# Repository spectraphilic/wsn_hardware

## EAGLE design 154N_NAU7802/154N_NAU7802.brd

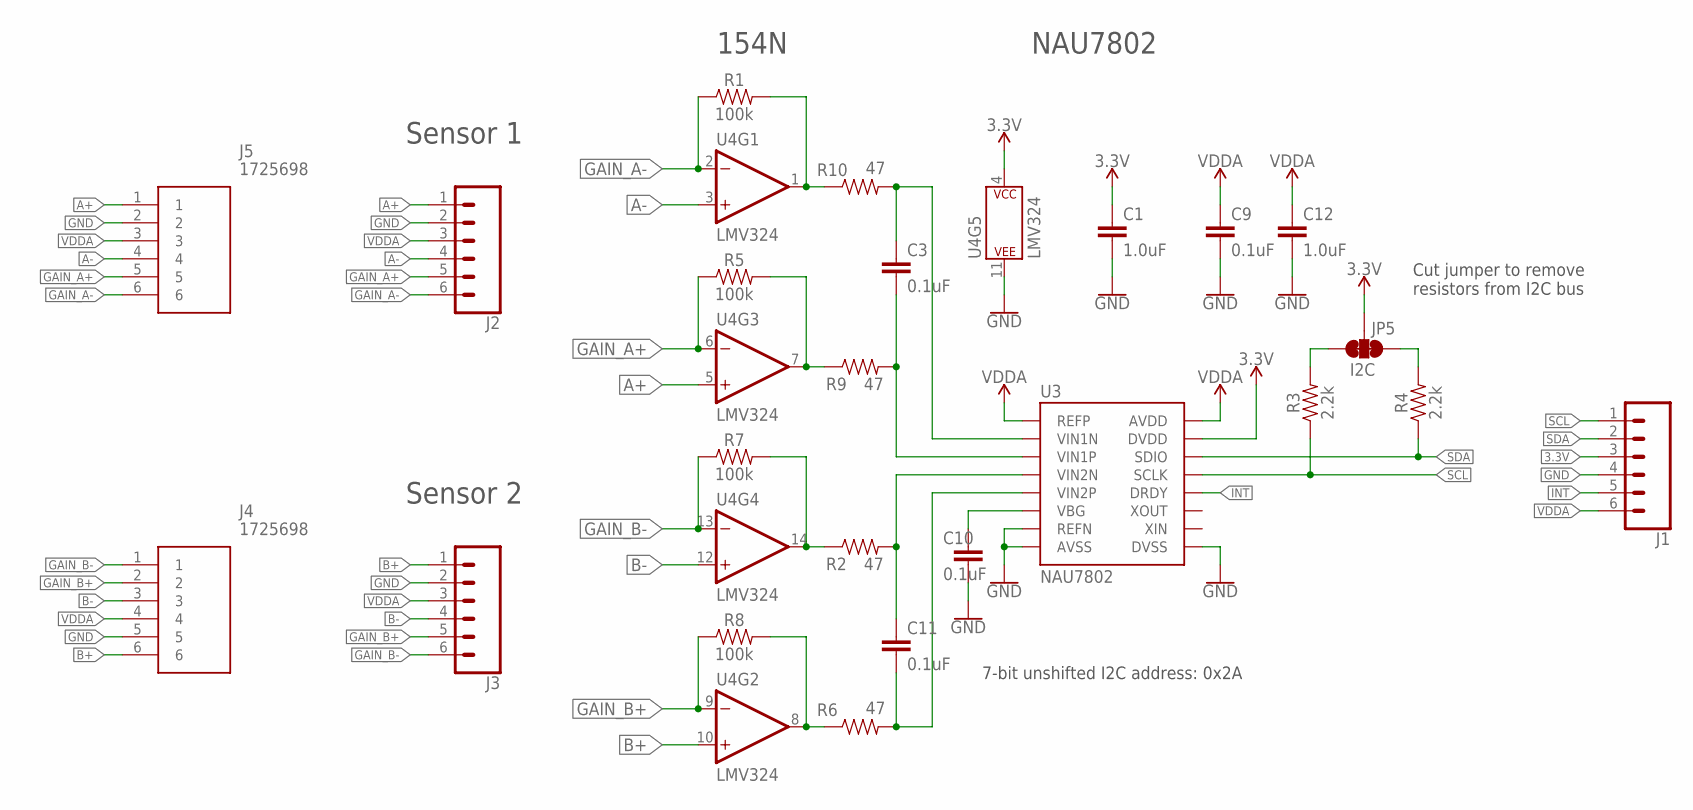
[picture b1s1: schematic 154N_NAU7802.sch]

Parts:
C1, C12: 1.0uF; 0603
C3, C9, C10, C11: 0.1uF; 0603
J1, J2, J3: CONN_06SILK_FEMALE_PTH; 1X06
J4, J5: 1725698; SHDR6W90P0X254_1X6_1570X620X85
JP5: I2C; SMT-JUMPER_3_2-NC_TRACE_SILK
R1, R5, R7, R8: 100k; 0603
R2, R6, R9, R10: 47; 0603
R3, R4: 2.2k; 0603
U3: NAU7802; SPARKFUN-IC-CONVERSION_SO16
U4: LMV324; SPARKFUN-IC-AMPLIFIERS_SO14

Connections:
3.3V: C1.1, J1.3, JP5.2, U3.15 (DVDD), U4.4 (P$V+)
A+: J2.1, J5.1, U4.5 (+IN)
A-: J2.4, J5.4, U4.3 (+IN)
B+: J3.1, J4.6, U4.10 (+IN)
B-: J3.4, J4.3, U4.12 (+IN)
GAIN_A+: J2.5, J5.5, R5.1, U4.6 (-IN)
GAIN_A-: J2.6, J5.6, R1.1, U4.2 (-IN)
GAIN_B+: J3.5, J4.2, R8.1, U4.9 (-IN)
GAIN_B-: J3.6, J4.1, R7.1, U4.13 (-IN)
GND: C1.2, C9.2, C10.2, C12.2, J1.4, J2.2, J3.2, J4.5, J5.2, U3.7 (REFN), U3.8 (AVSS), U3.9 (DVSS), U4.11 (P$V-)
INT: J1.5, U3.12 (DRDY)
unnamed: R6.1, R8.2, U4.8 (OUT)
unnamed: JP5.1, R4.2
unnamed: JP5.3, R3.2
unnamed: R2.1, R7.2, U4.14 (OUT)
unnamed: R1.2, R10.1, U4.1 (OUT)
unnamed: R5.2, R9.1, U4.7 (OUT)
unnamed: C10.1, U3.6 (VBG)
unnamed: C3.2, R9.2, U3.3 (VIN1P)
unnamed: C3.1, R10.2, U3.2 (VIN1N)
unnamed: C11.2, R6.2, U3.5 (VIN2P)
unnamed: C11.1, R2.2, U3.4 (VIN2N)
SCL: J1.1, R3.1, U3.13 (SCLK)
SDA: J1.2, R4.1, U3.14 (SDIO)
VDDA: C9.1, C12.1, J1.6, J2.3, J3.3, J4.4, J5.3, U3.1 (REFP), U3.16 (AVDD)

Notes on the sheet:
7-bit unshifted I2C address: 0x2A
Cut jumper to remove resistors from I2C bus
NAU7802
154N
Sensor 1
Sensor 2

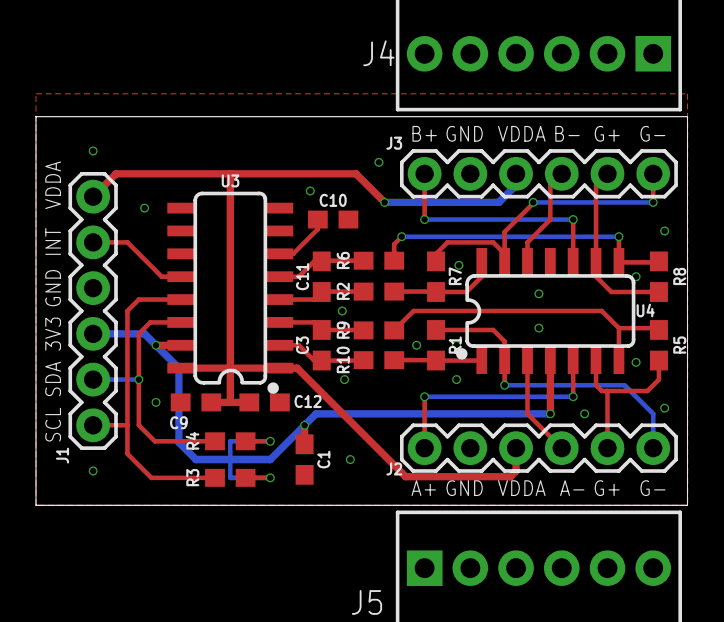
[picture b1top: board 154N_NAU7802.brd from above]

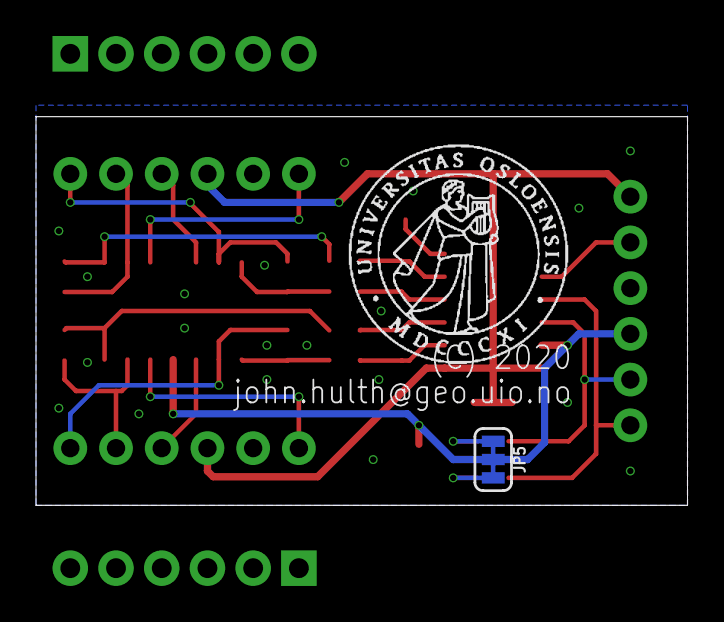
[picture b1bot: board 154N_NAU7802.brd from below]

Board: 2 copper layers, 36.2 x 21.6 mm, 25 parts (2 on the bottom side), 25 nets.

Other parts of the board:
U$3: UIO-LOGO-BL

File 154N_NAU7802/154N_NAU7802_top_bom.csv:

Comment,Designator,Footprint,LCSC Part #
0.1uF,C3 C9 C10 C11,0603,
1.0uF,C1 C12,0603,
2.2k,R3 R4,0603,
47,R2 R6 R9 R10,0603,
100k,R1 R5 R7 R8,0603,
LMV324,U4,SPARKFUN-IC-AMPLIFIERS_SO14,
MCP604SL,IC1,SO14,
NAU7802,U3,SPARKFUN-IC-CONVERSION_SO16,

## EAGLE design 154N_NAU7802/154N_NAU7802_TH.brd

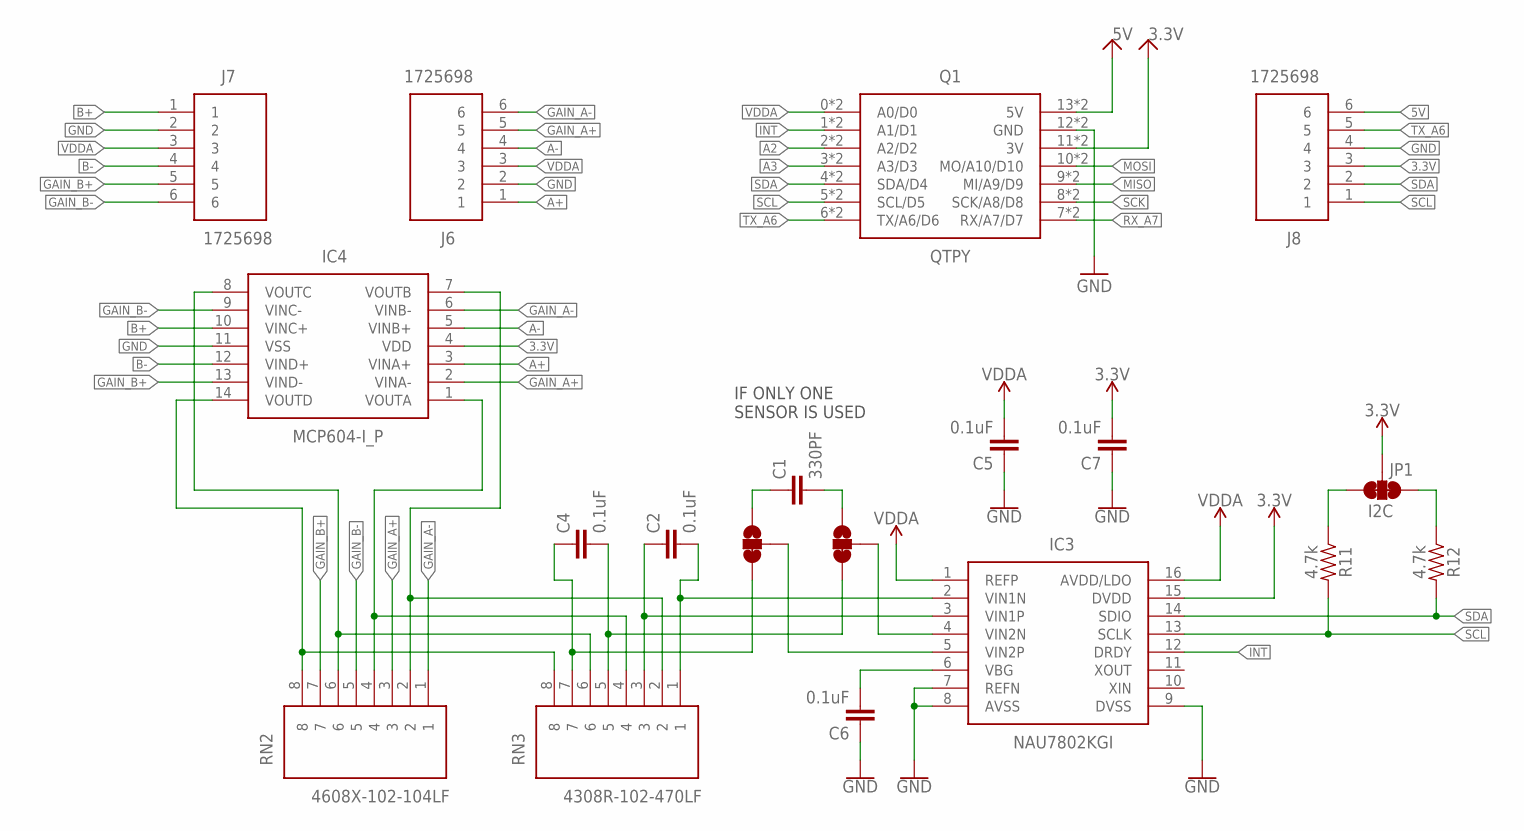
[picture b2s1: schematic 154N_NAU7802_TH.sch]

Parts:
C1: 330PF; CAP-PTH-SMALL-KIT
C2, C4, C5, C6, C7: 0.1uF; CAP-PTH-SMALL-KIT
IC3: NAU7802KGI; DIP792W51P254L1905H53Q16N
IC4: MCP604-I_P; DIP781W56P254L1918H533Q14N
J6, J7, J8: 1725698; SHDR6W90P0X254_1X6_1570X620X85
JP1: I2C; SMT-JUMPER_3_2-NC_TRACE_SILK
JP4, JP5: JUMPER-SMT_3_1-NC_TRACE_NO-SILK; SMT-JUMPER_3_1-NC_TRACE_NO-SILK
Q1: QTPY
R11, R12: 4.7k; AXIAL-0.3
RN2: 4608X-102-104LF; 4608X102104LF
RN3: 4308R-102-470LF; 4308R102470LF

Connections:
3.3V: C7.2, IC3.15 (DVDD), IC4.4 (VDD), J8.3, JP1.2, Q1.11 (3V), Q1.11C (3V)
5V: J8.6, Q1.13 (5V), Q1.13C (5V)
A2: Q1.2 (A2/D2), Q1.2C (A2/D2)
A3: Q1.3 (A3/D3), Q1.3C (A3/D3)
A+: IC4.3 (VINA+), J6.1
A-: IC4.5 (VINB+), J6.4
B+: IC4.10 (VINC+), J7.1
B-: IC4.12 (VIND+), J7.4
GAIN_A+: IC4.2 (VINA-), J6.5, RN2.3
GAIN_A-: IC4.6 (VINB-), J6.6, RN2.1
GAIN_B+: IC4.13 (VIND-), J7.5, RN2.7
GAIN_B-: IC4.9 (VINC-), J7.6, RN2.5
GND: C5.1, C6.1, C7.1, IC3.7 (REFN), IC3.8 (AVSS), IC3.9 (DVSS), IC4.11 (VSS), J6.2, J7.2, J8.4, Q1.12 (GND), Q1.12C (GND)
INT: IC3.12 (DRDY), Q1.1 (A1/D1), Q1.1C (A1/D1)
MISO: Q1.9 (MI/A9/D9), Q1.9C (MI/A9/D9)
MOSI: Q1.10 (MO/A10/D10), Q1.10C (MO/A10/D10)
unnamed: C1.2, JP4.1
unnamed: C2.2, IC3.2 (VIN1N), RN3.1
unnamed: C1.1, JP5.1
unnamed: IC3.4 (VIN2N), JP4.2
unnamed: C2.1, IC3.3 (VIN1P), RN3.3
unnamed: IC3.5 (VIN2P), JP5.2
unnamed: C4.2, JP4.3, RN3.5
unnamed: C4.1, JP5.3, RN3.7
unnamed: IC4.7 (VOUTB), RN2.2, RN3.2
unnamed: IC4.1 (VOUTA), RN2.4, RN3.4
unnamed: IC4.8 (VOUTC), RN2.6, RN3.6
unnamed: IC4.14 (VOUTD), RN2.8, RN3.8
unnamed: C6.2, IC3.6 (VBG)
unnamed: JP1.1, R12.P$1 (1)
unnamed: JP1.3, R11.P$1 (1)
RX_A7: Q1.7 (RX/A7/D7), Q1.7C (RX/A7/D7)
SCK: Q1.8 (SCK/A8/D8), Q1.8C (SCK/A8/D8)
SCL: IC3.13 (SCLK), J8.1, Q1.5 (SCL/D5), Q1.5C (SCL/D5), R11.P$2 (2)
SDA: IC3.14 (SDIO), J8.2, Q1.4 (SDA/D4), Q1.4C (SDA/D4), R12.P$2 (2)
TX_A6: J8.5, Q1.6 (TX/A6/D6), Q1.6C (TX/A6/D6)
VDDA: C5.2, IC3.1 (REFP), IC3.16 (AVDD/LDO), J6.3, J7.3, Q1.0 (A0/D0), Q1.0C (A0/D0)

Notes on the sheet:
IF ONLY ONE SENSOR IS USED

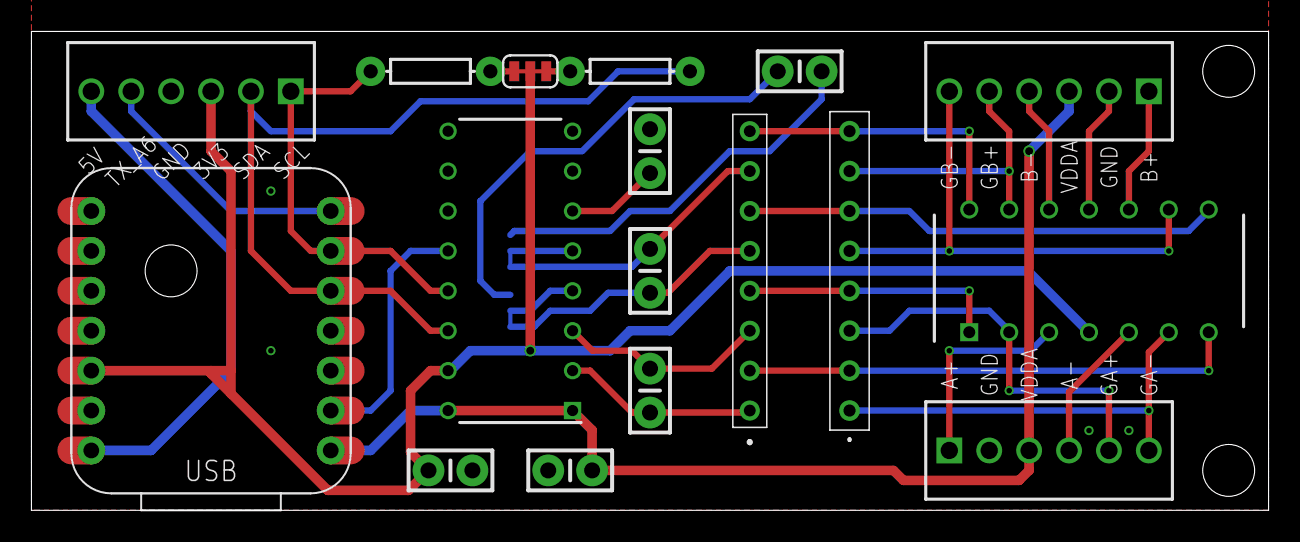
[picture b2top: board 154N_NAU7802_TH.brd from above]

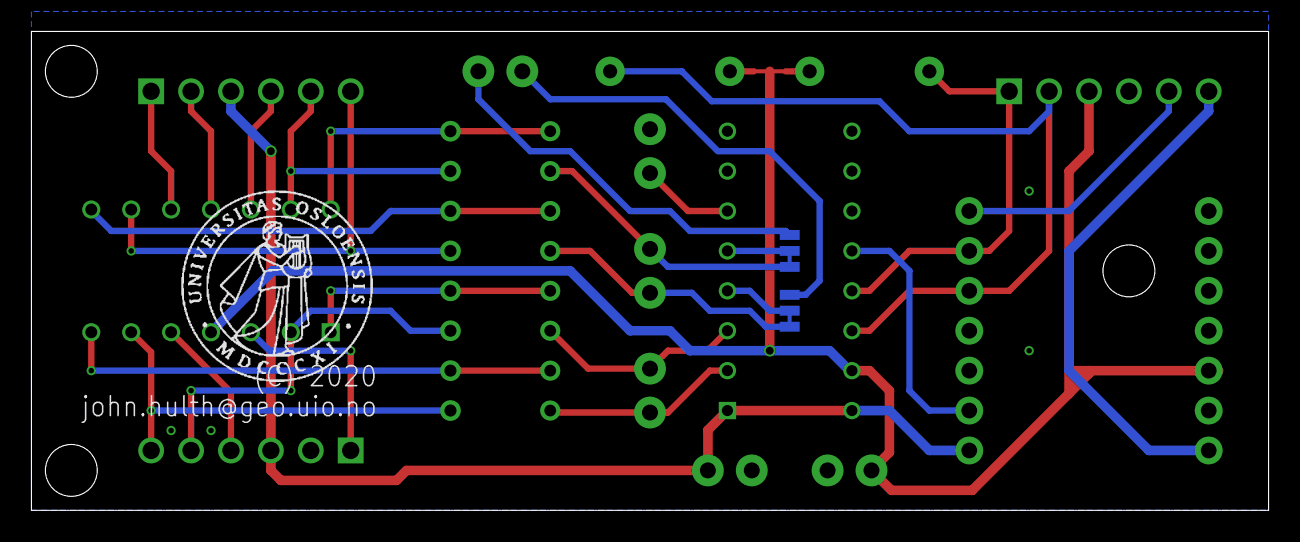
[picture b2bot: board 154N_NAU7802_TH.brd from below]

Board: 2 copper layers, 78.7 x 30.5 mm, 23 parts (3 on the bottom side), 37 nets.

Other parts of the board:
JP2, JP3, JP8: STAND-OFF
U$6: UIO-LOGO-BL

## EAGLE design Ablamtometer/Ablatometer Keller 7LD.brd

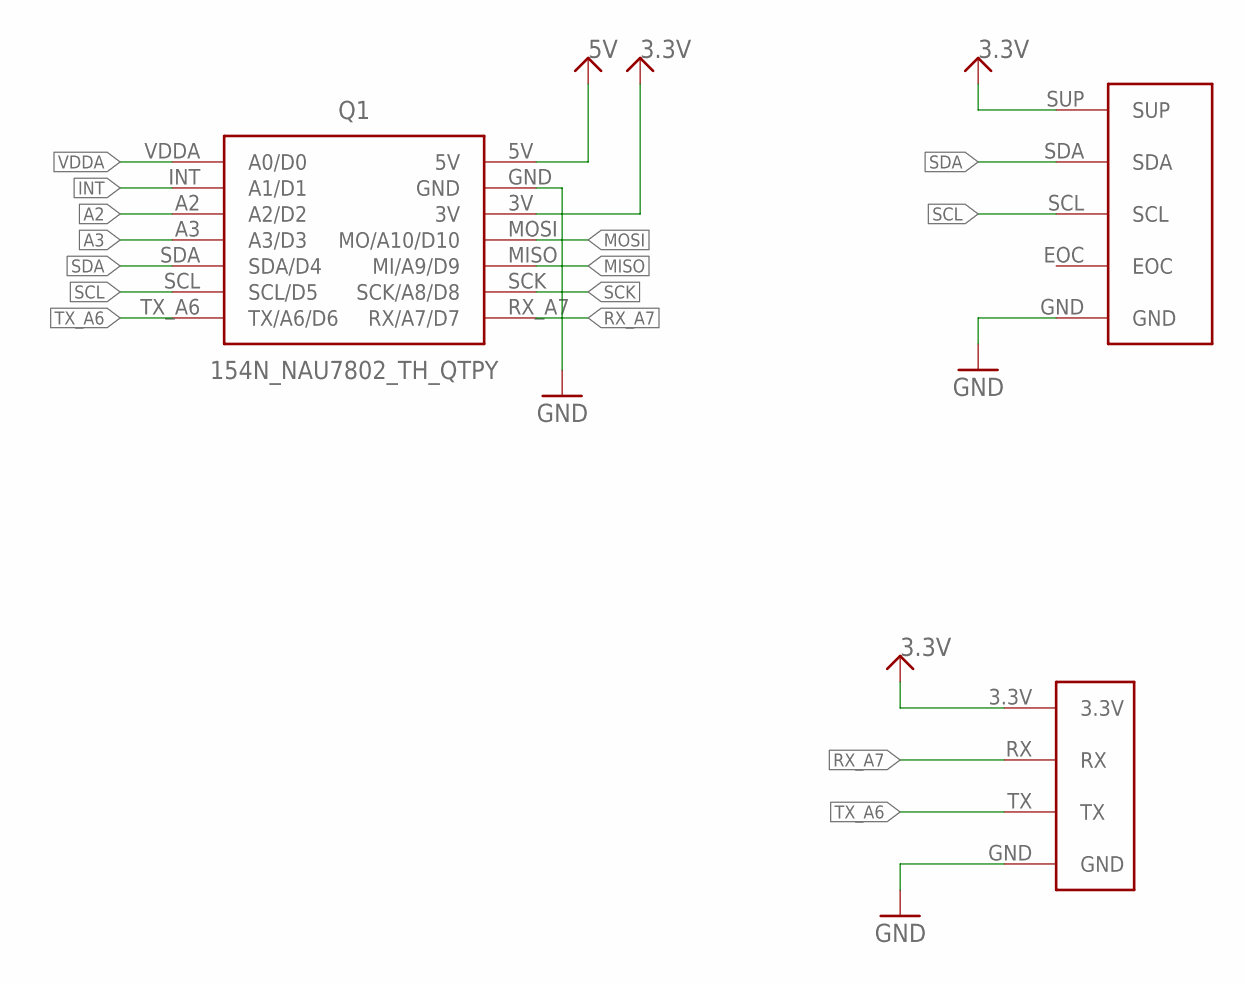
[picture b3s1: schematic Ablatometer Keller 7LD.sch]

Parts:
Q1: 154N_NAU7802_TH_QTPY
U$1: KELLER_7LD
U$3: WIRE_PADS

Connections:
3.3V: Q1.3V, U$1.SUP, U$3.3.3V
5V: Q1.5V
A2: Q1.A2 (A2/D2)
A3: Q1.A3 (A3/D3)
GND: Q1.GND, U$1.GND, U$3.GND
INT: Q1.INT (A1/D1)
MISO: Q1.MISO (MI/A9/D9)
MOSI: Q1.MOSI (MO/A10/D10)
RX_A7: Q1.RX_A7 (RX/A7/D7), U$3.RX
SCK: Q1.SCK (SCK/A8/D8)
SCL: Q1.SCL (SCL/D5), U$1.SCL
SDA: Q1.SDA (SDA/D4), U$1.SDA
TX_A6: Q1.TX_A6 (TX/A6/D6), U$3.TX
VDDA: Q1.VDDA (A0/D0)

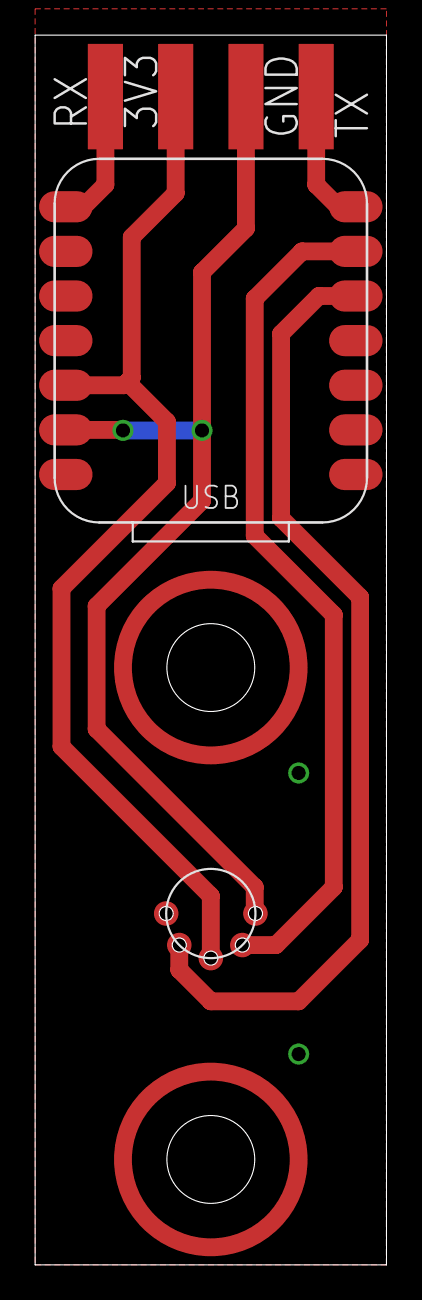
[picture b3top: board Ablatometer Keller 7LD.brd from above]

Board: 2 copper layers, 20.0 x 70.0 mm, 4 parts (1 on the bottom side), 6 nets.

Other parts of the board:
U$6: UIO-LOGO-BL

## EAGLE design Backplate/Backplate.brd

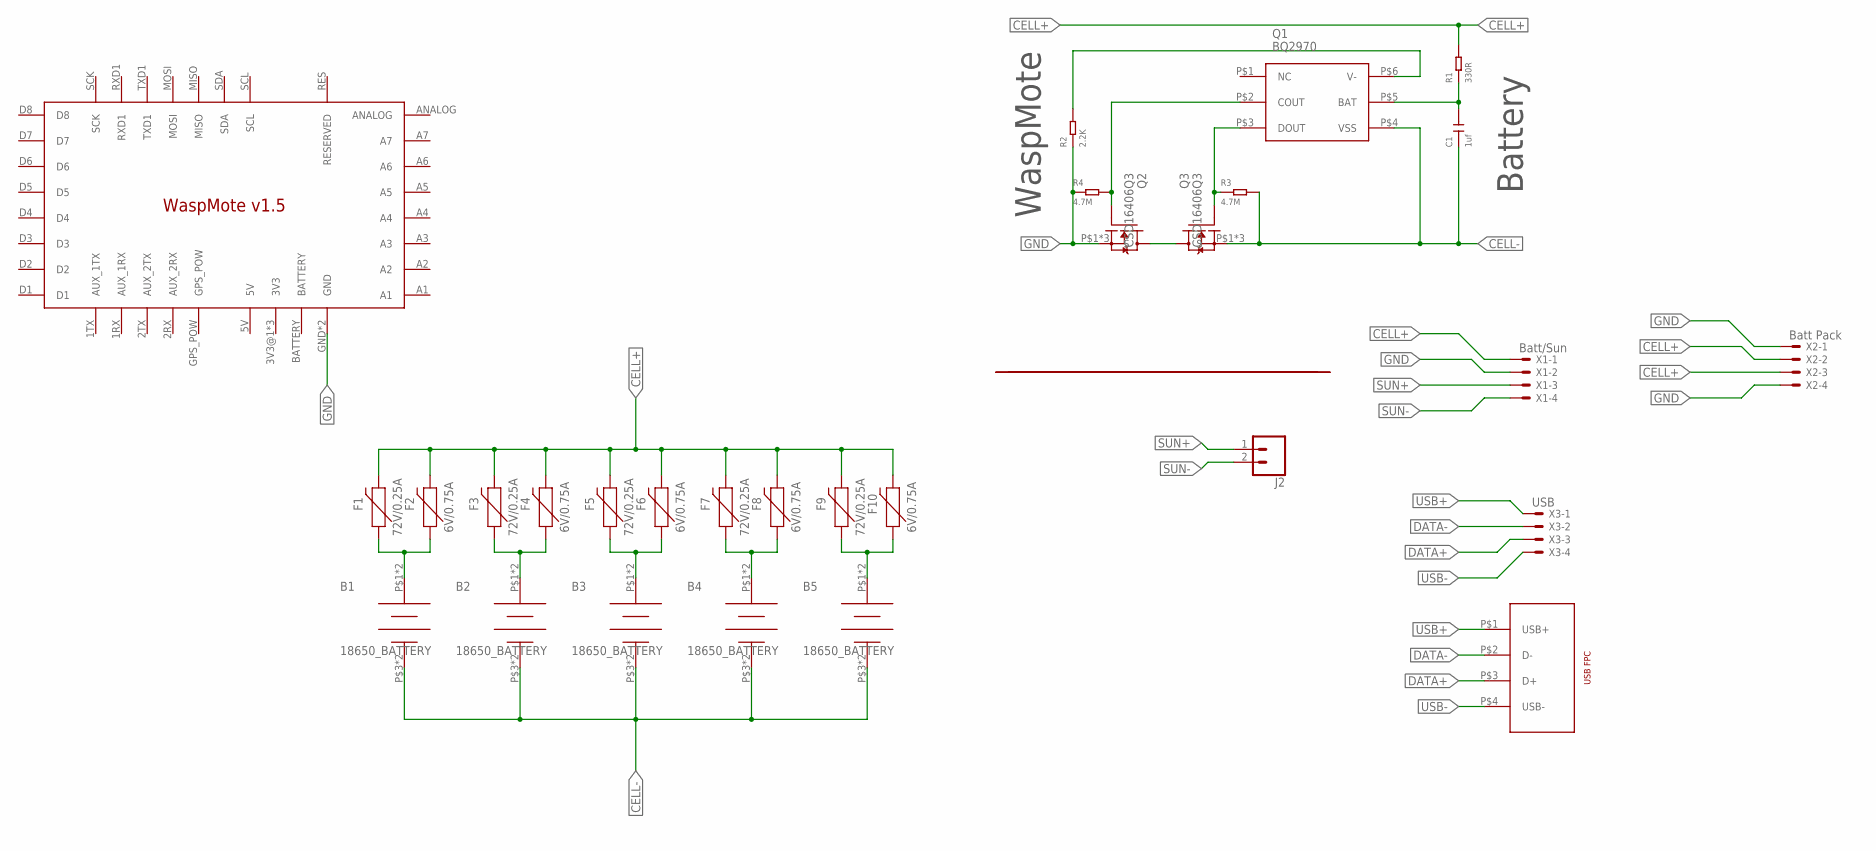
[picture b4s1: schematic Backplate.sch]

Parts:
B1, B2, B3, B4, B5: 18650_BATTERY; 18650_BATTERY_HOLDER
C1: 1uf; C0603
F1, F3, F5, F7, F9: 72V/0.25A; PTH
F2, F4, F6, F8, F10: 6V/0.75A; 1206
J1: USB_FTP; 1MM_FPC
J2: CONN_023.5MM_LOCK; SCREWTERMINAL-3.5MM-2_LOCK
Q1: BQ2970; WSON-6; MPN BQ2970
Q2, Q3: CSD16406Q3
R1: 330R; R0603
R2: 2.2K; R0603
R3, R4: 4.7M; R0603
U$12: WASPMOTE_V1.5
X1: Batt/Sun; 22-23-2041
X2: Batt Pack; 22-23-2041
X3: USB; 22-23-2041

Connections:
CELL+: F1.P$2 (2), F2.2, F3.P$2 (2), F4.2, F5.P$2 (2), F6.2, F7.P$2 (2), F8.2, F9.P$2 (2), F10.2, R1.2, X1.1, X2.2, X2.3
CELL-: B1.P$3 (BATT-), B1.P$4 (BATT-), B2.P$3 (BATT-), B2.P$4 (BATT-), B3.P$3 (BATT-), B3.P$4 (BATT-), B4.P$3 (BATT-), B4.P$4 (BATT-), B5.P$3 (BATT-), B5.P$4 (BATT-), C1.1, Q1.P$4 (VSS), Q3.P$1 (S), Q3.P$2 (S), Q3.P$3 (S), R3.2
D: Q2.P$5 (D), Q2.P$6 (D), Q2.P$7 (D), Q2.P$8 (D), Q3.P$5 (D), Q3.P$6 (D), Q3.P$7 (D), Q3.P$8 (D)
DATA+: J1.P$3 (D+), X3.3
DATA-: J1.P$2 (D-), X3.2
GND: Q2.P$1 (S), Q2.P$2 (S), Q2.P$3 (S), R2.1, R4.1, U$12.GND, U$12.GND_2 (GND), X1.2, X2.1, X2.4
unnamed: Q1.P$3 (DOUT), Q3.P$4 (G), R3.1
unnamed: B1.P$1 (BATT+), B1.P$2 (BATT+), F1.P$1 (1), F2.1
unnamed: B2.P$1 (BATT+), B2.P$2 (BATT+), F3.P$1 (1), F4.1
unnamed: B3.P$1 (BATT+), B3.P$2 (BATT+), F5.P$1 (1), F6.1
unnamed: B4.P$1 (BATT+), B4.P$2 (BATT+), F7.P$1 (1), F8.1
unnamed: B5.P$1 (BATT+), B5.P$2 (BATT+), F9.P$1 (1), F10.1
unnamed: Q1.P$2 (COUT), Q2.P$4 (G), R4.2
unnamed: Q1.P$6 (V-), R2.2
unnamed: C1.2, Q1.P$5 (BAT), R1.1
SUN+: J2.1, X1.3
SUN-: J2.2, X1.4
USB+: J1.P$1 (USB+), X3.1
USB-: J1.P$4 (USB-), X3.4

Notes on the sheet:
Battery
WaspMote

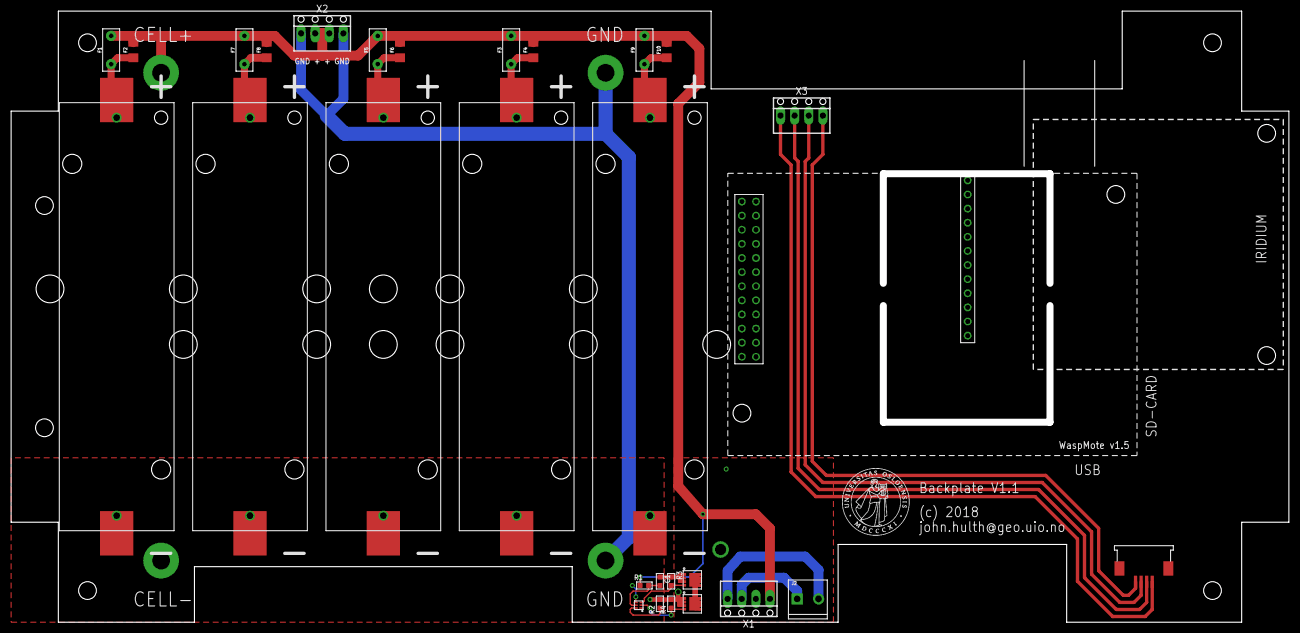
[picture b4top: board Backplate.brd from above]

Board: 2 copper layers, 230.0 x 110.0 mm, 30 parts (0 on the bottom side), 19 nets.

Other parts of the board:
U$1: UIO-LOGO-BL

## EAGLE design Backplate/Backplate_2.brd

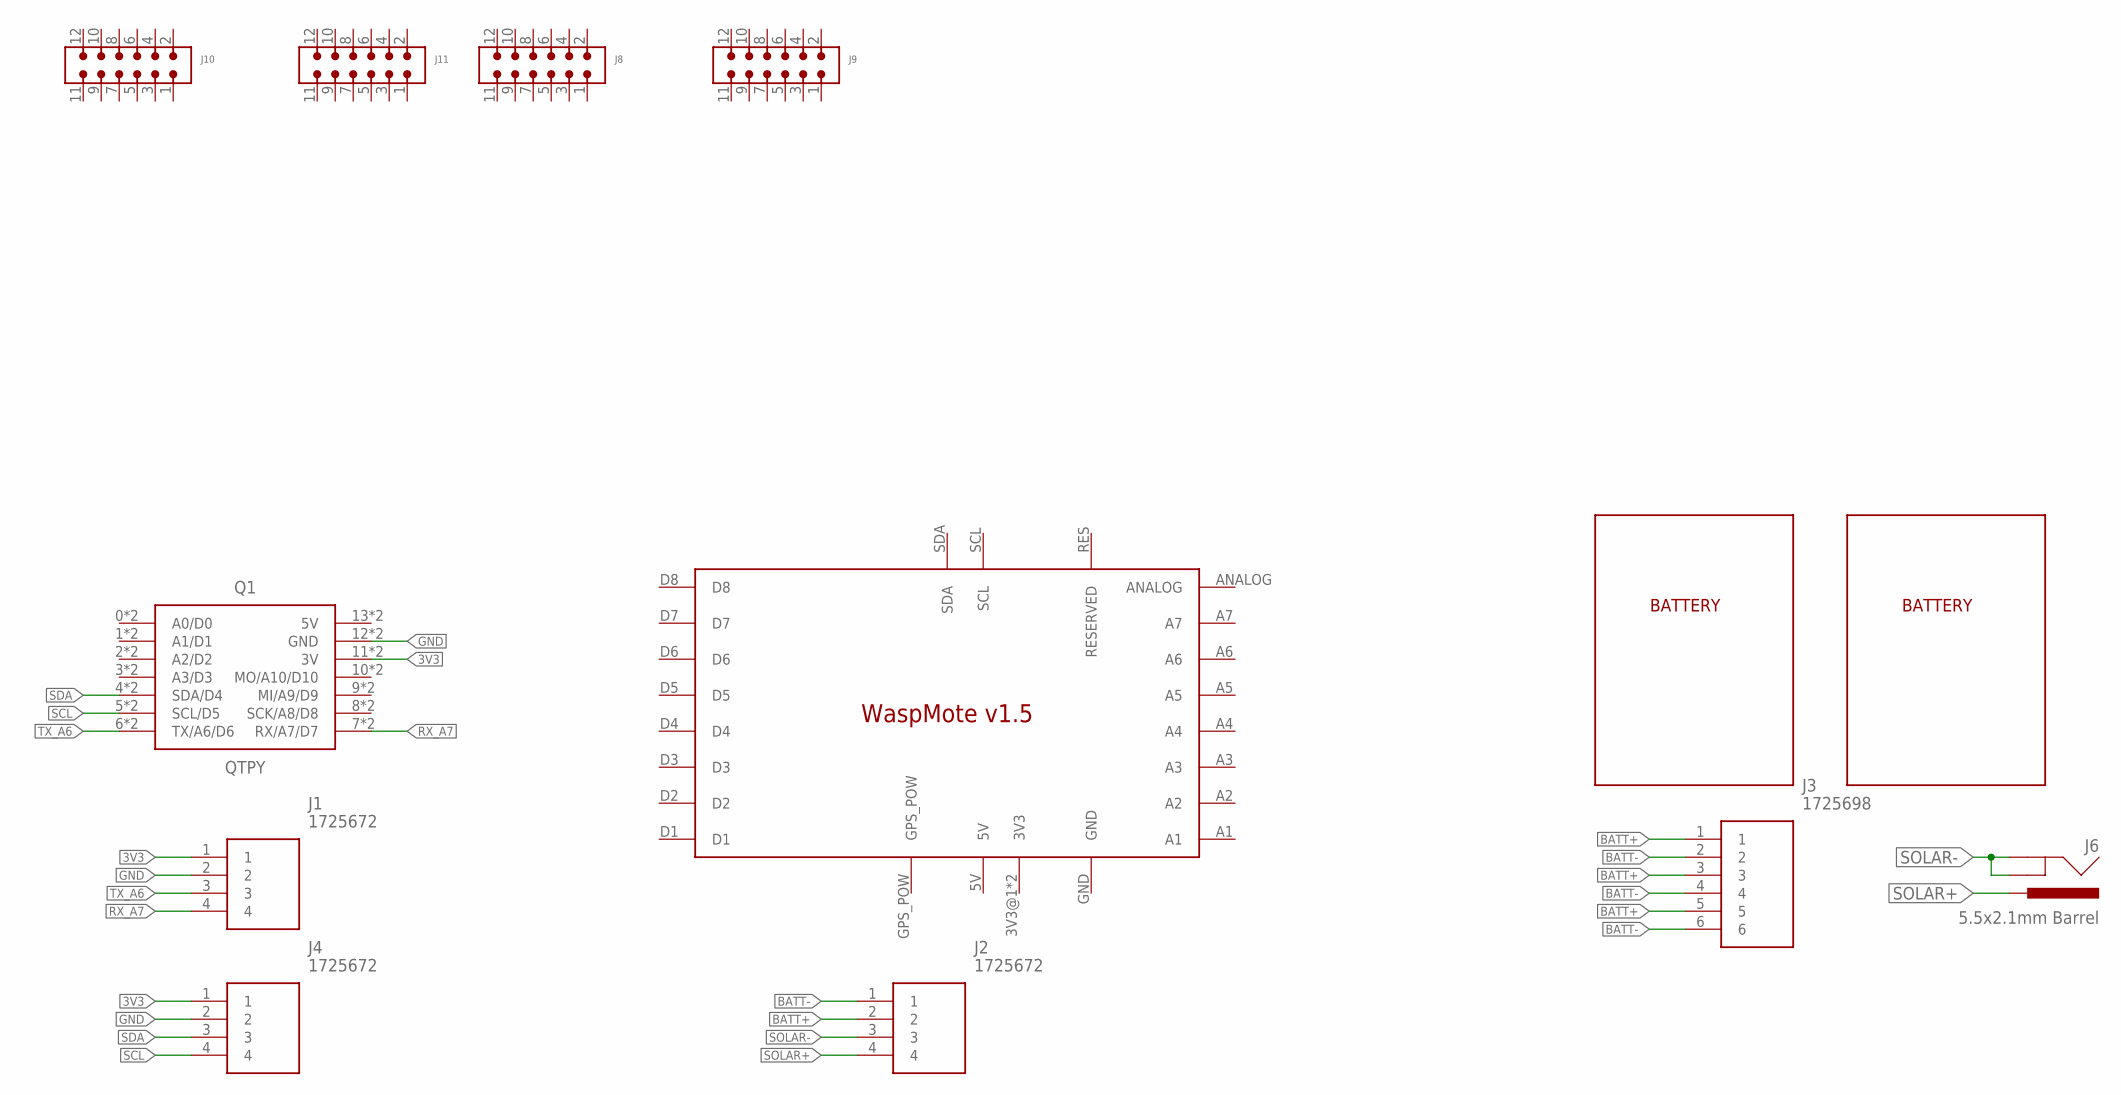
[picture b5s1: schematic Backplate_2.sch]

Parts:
J1, J2, J4: 1725672; 1725672-4-2.54
J3: 1725698; SHDR6W90P0X254_1X6_1570X620X85
J6: 5.5x2.1mm Barrel; POWER_JACK_PTH
J8, J9, J10, J11: 6130XX21021_61301221021; 61301221021
Q1: QTPY
U$1, U$2: BATTERY
U$12: WASPMOTE_V1.5

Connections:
3V3: J1.1, J4.1, Q1.11 (3V), Q1.11C (3V)
BATT+: J2.2, J3.1, J3.3, J3.5
BATT-: J2.1, J3.2, J3.4, J3.6
GND: J1.2, J4.2, Q1.12 (GND), Q1.12C (GND)
RX_A7: J1.4, Q1.7 (RX/A7/D7), Q1.7C (RX/A7/D7)
SCL: J4.4, Q1.5 (SCL/D5), Q1.5C (SCL/D5)
SDA: J4.3, Q1.4 (SDA/D4), Q1.4C (SDA/D4)
SOLAR+: J2.4, J6.PWR
SOLAR-: J2.3, J6.GND, J6.GNDBREAK
TX_A6: J1.3, Q1.6 (TX/A6/D6), Q1.6C (TX/A6/D6)

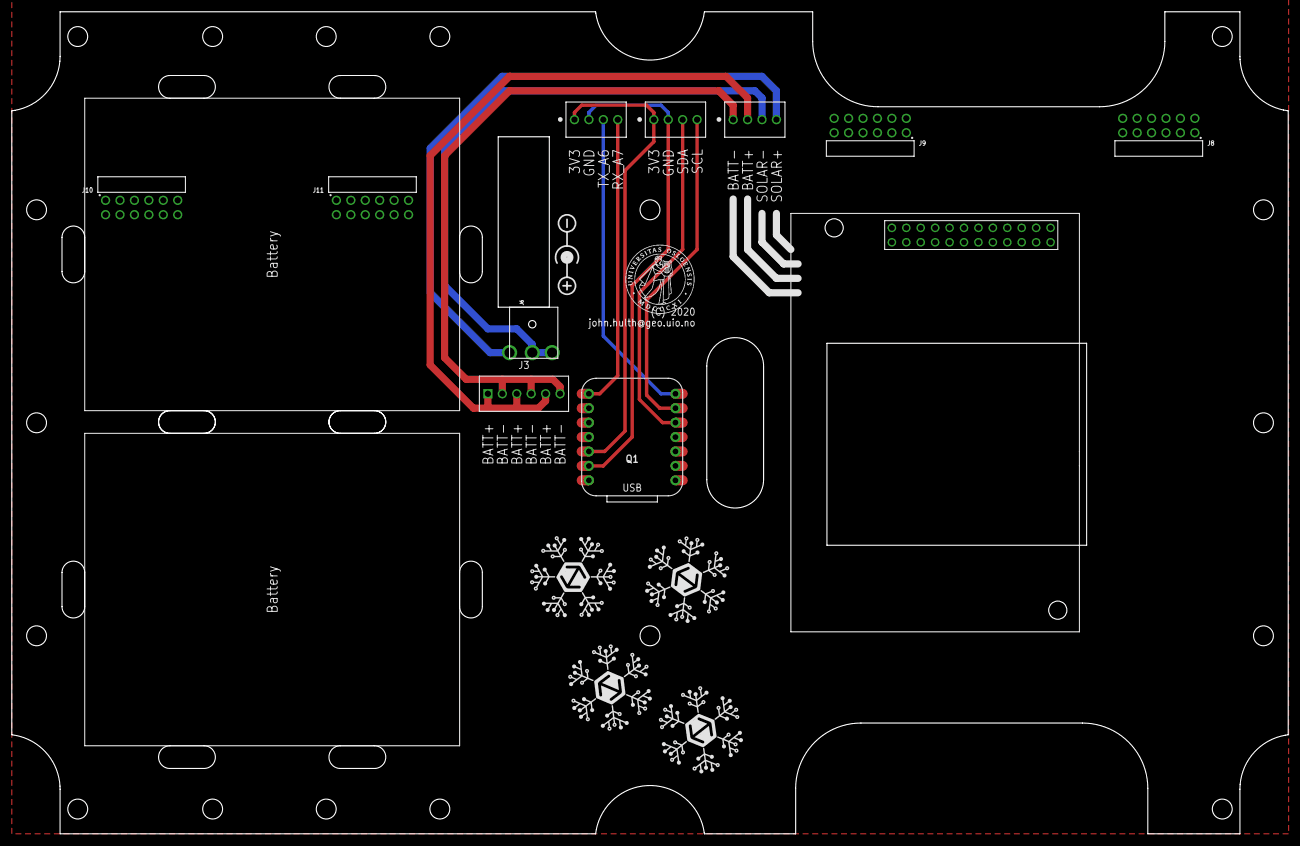
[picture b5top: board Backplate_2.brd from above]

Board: 2 copper layers, 224.7 x 144.7 mm, 18 parts (0 on the bottom side), 10 nets.

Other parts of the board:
U$3: UIO-LOGO-BL
U$4, U$5, U$6, U$7: HIVE-LOGO

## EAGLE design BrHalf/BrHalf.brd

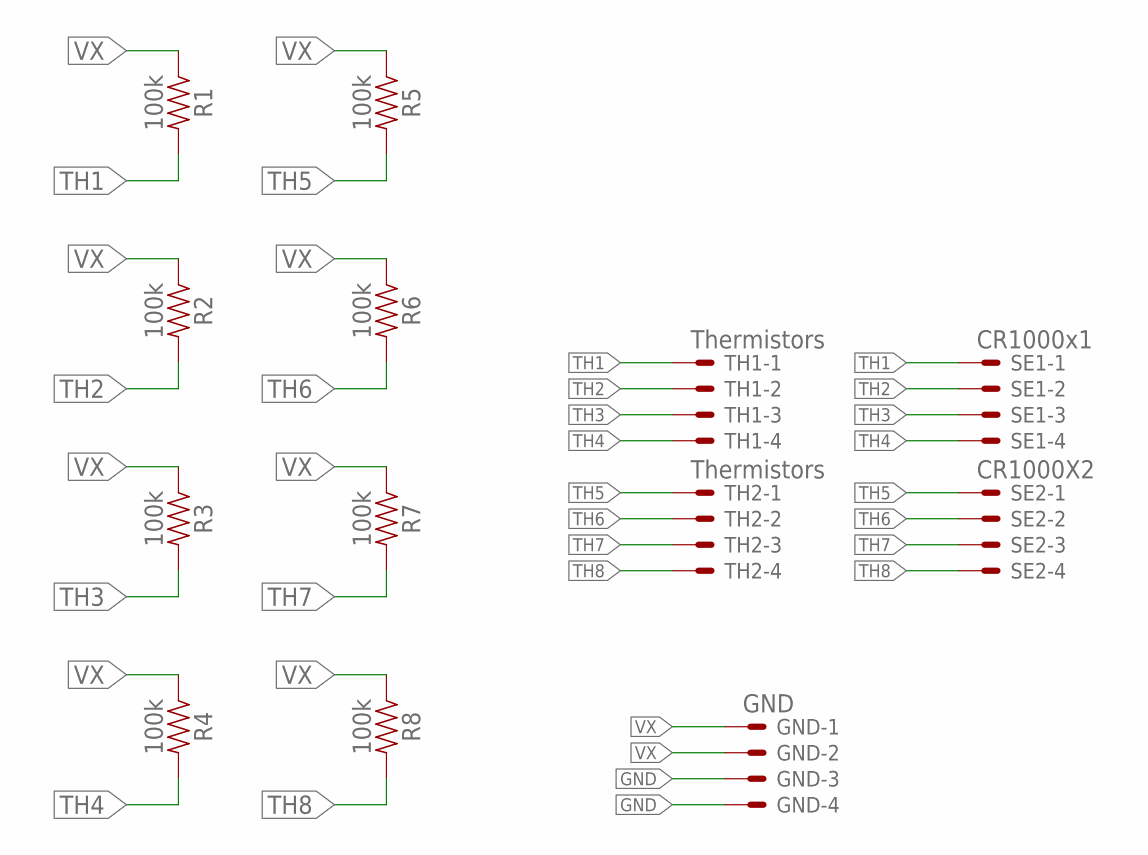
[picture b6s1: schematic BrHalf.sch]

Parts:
GND: GND; 22-23-2041
R1, R2, R3, R4, R5, R6, R7, R8: 100k; AXIAL-0.3
SE1: CR1000x1; 22-23-2041
SE2: CR1000X2; 22-23-2041
TH1, TH2: Thermistors; 22-23-2041

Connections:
GND: GND.3, GND.4
TH1: R1.P$2 (2), SE1.1, TH1.1
TH2: R2.P$2 (2), SE1.2, TH1.2
TH3: R3.P$2 (2), SE1.3, TH1.3
TH4: R4.P$2 (2), SE1.4, TH1.4
TH5: R5.P$2 (2), SE2.1, TH2.1
TH6: R6.P$2 (2), SE2.2, TH2.2
TH7: R7.P$2 (2), SE2.3, TH2.3
TH8: R8.P$2 (2), SE2.4, TH2.4
VX: GND.1, GND.2, R1.P$1 (1), R2.P$1 (1), R3.P$1 (1), R4.P$1 (1), R5.P$1 (1), R6.P$1 (1), R7.P$1 (1), R8.P$1 (1)

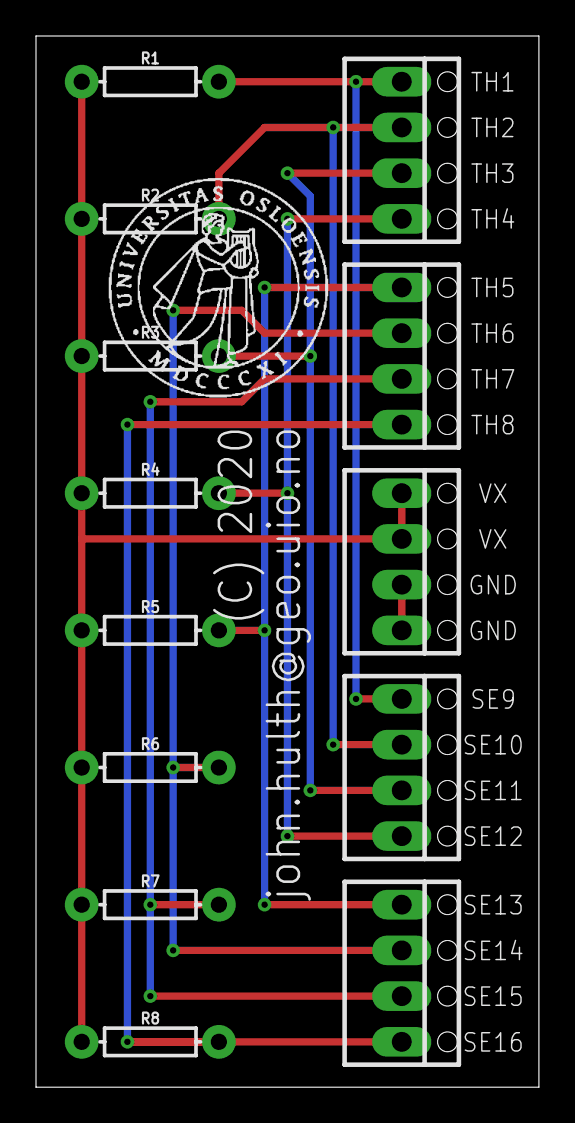
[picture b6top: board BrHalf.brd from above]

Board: 2 copper layers, 27.9 x 58.4 mm, 14 parts (0 on the bottom side), 10 nets.

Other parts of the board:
U$3: UIO-LOGO-BL

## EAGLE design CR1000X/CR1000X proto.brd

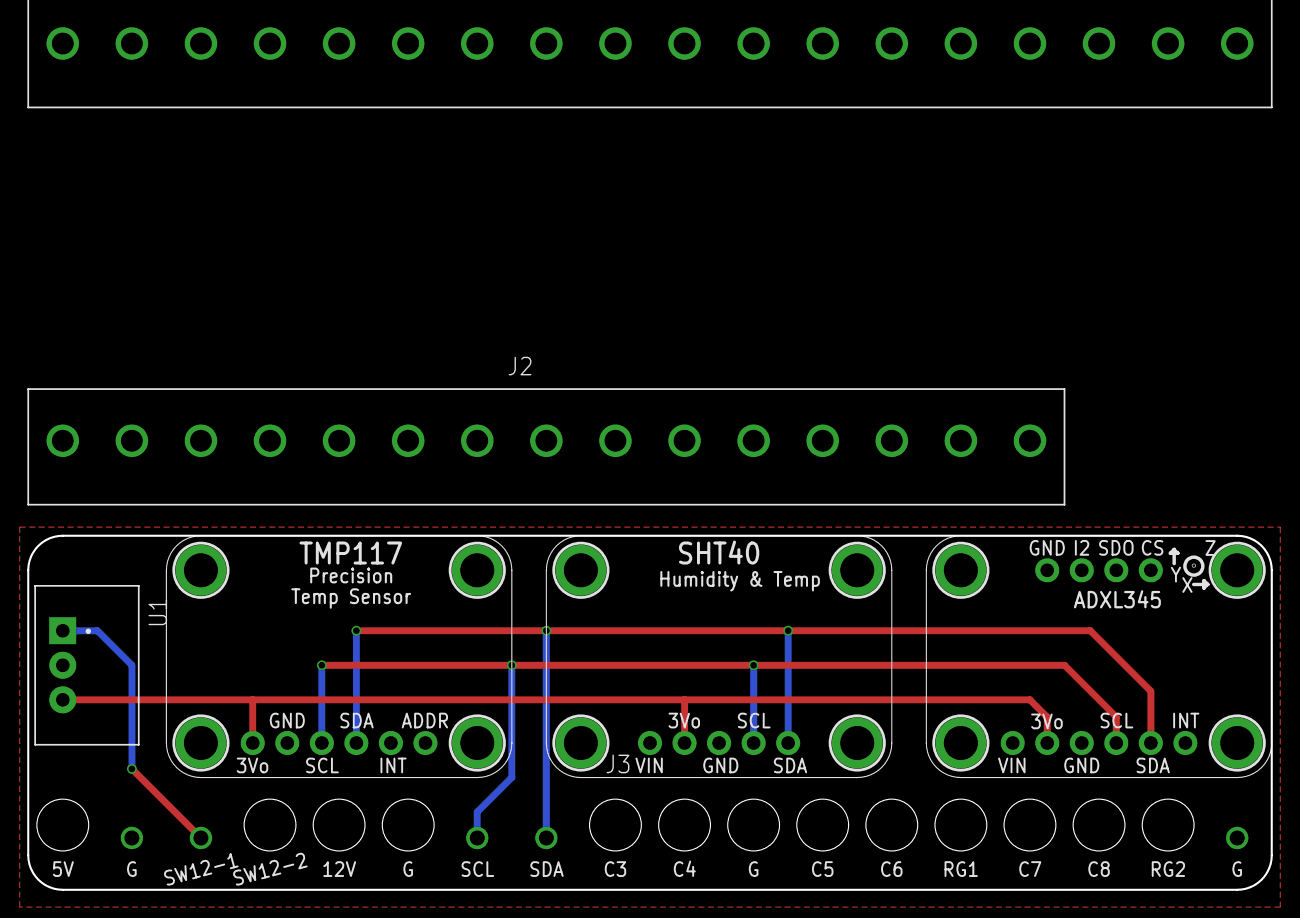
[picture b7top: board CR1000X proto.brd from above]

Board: 2 copper layers, 91.4 x 26.0 mm, 21 parts (1 on the bottom side), 5 nets.

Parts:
J1: 691311500018
J2: 691311500015
J3: WURTH_ELEKTRONIK_ELECTROMECHANIC_TERMINAL_BLOCKS_CONNECTORS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
JP2, JP7: 1X06_ROUND_70
JP4: 1X05_ROUND_70
JP8: 1X04_ROUND
U1: 173010535
U$3, U$4, U$6, U$7, U$22, U$23, U$25, U$26, U$36, U$37, U$39, U$40: MOUNTINGHOLE2.5; MOUNTINGHOLE_2.5_PLATED
U$9: UIO-LOGO-BL

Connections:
3.3V: JP2.1, JP4.2, JP7.2, U1.3
GND: J3.2, JP2.2, JP4.3, JP7.3, JP8.1, U1.2
SCL: J3.7, JP2.3, JP4.4, JP7.4
SDA: J3.8, JP2.4, JP4.5, JP7.5
SW12-1: J3.3, U1.1

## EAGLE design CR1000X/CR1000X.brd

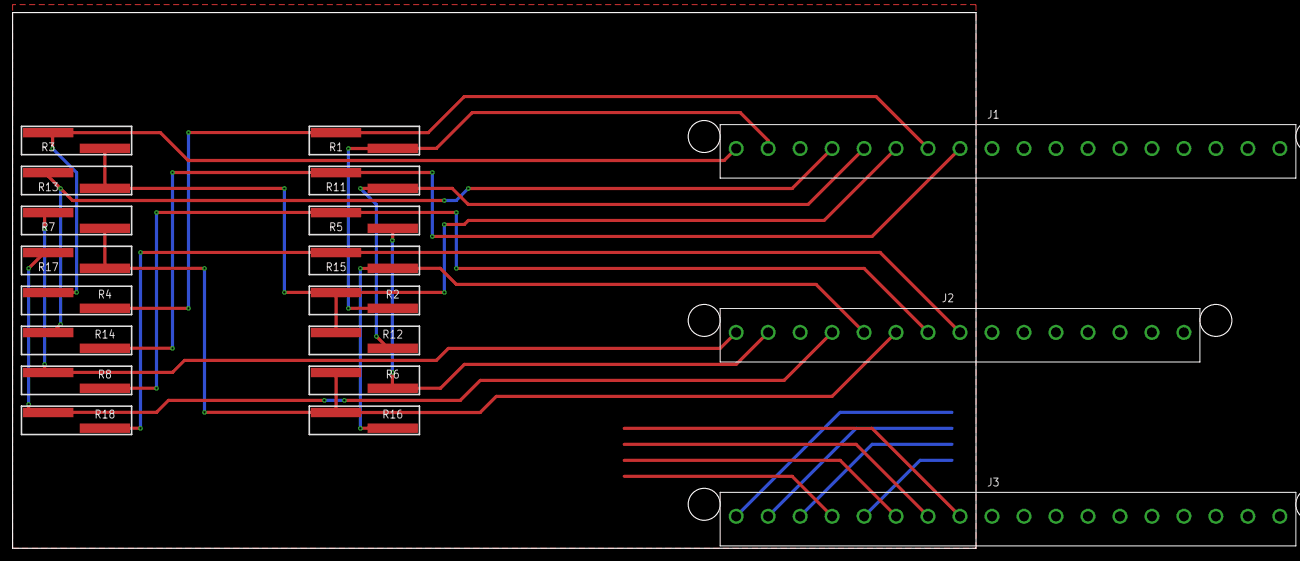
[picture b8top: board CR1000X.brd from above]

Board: 2 copper layers, 153.0 x 85.1 mm, 19 parts (0 on the bottom side), 14 nets.

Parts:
J1, J3: 691311500018
J2: 691311500015
R1, R2, R3, R4, R5, R6, R7, R8, R11, R12, R13, R14, R15, R16, R17, R18: STRAIN_GAUGE-5; STRAIN_GAUGE

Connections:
1H: J1.1, R3.1, R4.2
1L: J1.2, R1.2, R2.1
2H: J1.4, R13.1, R14.2
2L: J1.5, R11.2, R12.1
5H: J2.1, R7.1, R8.2
5L: J2.2, R5.2, R6.1
6H: J2.4, R17.1, R18.2
6L: J2.5, R15.2, R16.1
SG2: J1.6, R2.2, R3.2, R12.2, R13.2
SG6: J2.6, R6.2, R7.2, R16.2, R17.2
VX1: J1.7, R1.1, R4.1
VX2: J1.8, R11.1, R14.1
VX3: J2.7, R5.1, R8.1
VX4: J2.8, R15.1, R18.1

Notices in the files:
154N_NAU7802/154N_NAU7802.brd:
(C) 2020
Ablamtometer/Ablatometer Keller 7LD.brd:
(C) 2022
Backplate/Backplate.brd:
(c) 2018
parts and their libraries:
SparkFun-Capacitors: Licensing: Creative Commons ShareAlike 4.0 International - https://creativecommons.org/licenses/by-sa/4.0
microbuilder: This work is placed in the public domain, and may be freely used for commercial and non-commercial work with the following conditions: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
